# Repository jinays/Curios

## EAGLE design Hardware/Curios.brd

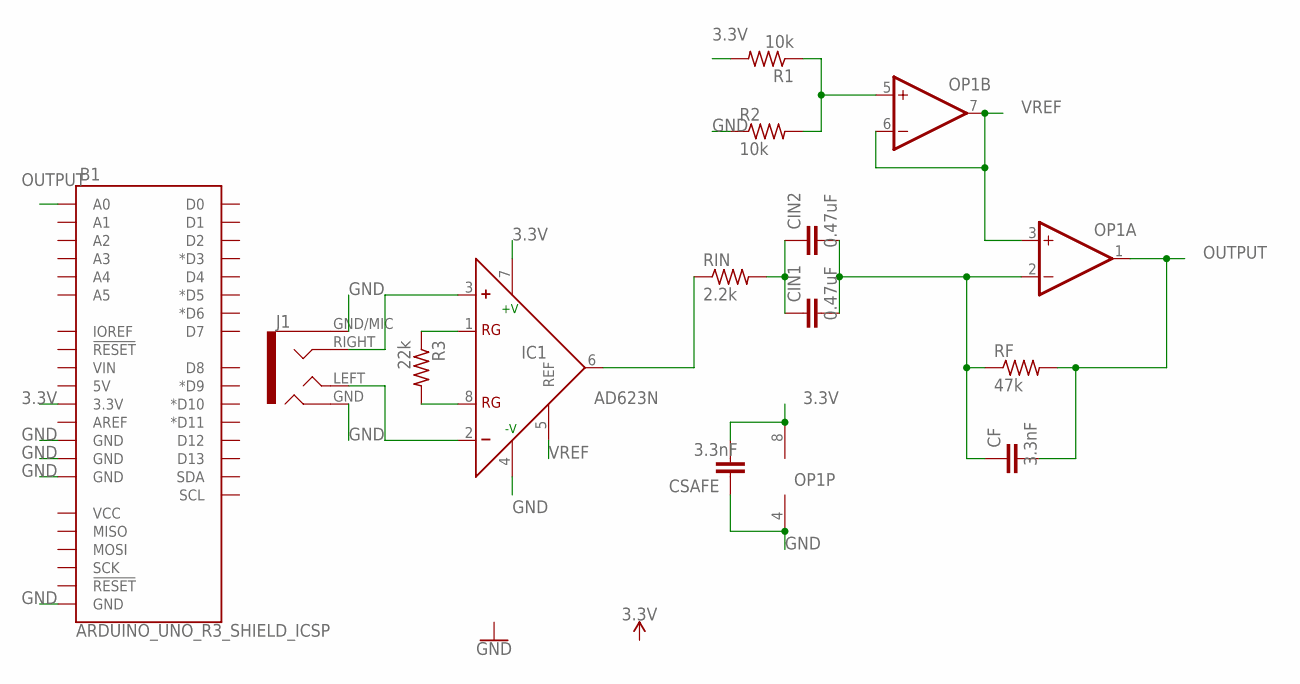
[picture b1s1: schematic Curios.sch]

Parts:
B1: ARDUINO_UNO_R3_SHIELD_ICSP; UNO_R3_SHIELD_ICSP
CF: 3.3nF; C0603
CIN1, CIN2: 0.47uF; C0603
CSAFE: 3.3nF; C0603
IC1: AD623N; DIL08
J1: AUDIO_JACK_TRRSSMD_RA; AUDIO_JACK_3.5MM_TRRS_SMD_RA
OP1: OP-DUALR; SO8
R1, R2: 10k; R0603
R3: 22k; R0603
RF: 47k; R0603
RIN: 2.2k; R0603

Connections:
3.3V: B1.3.3V, CSAFE.2, IC1.7 (+V), OP1.8 (V+), R1.2
GND: B1.GND@0 (GND), B1.GND@1 (GND), B1.GND@2 (GND), B1.GND_ICSP (GND), CSAFE.1, IC1.4 (-V), J1.GND (RING2), J1.GND/MIC (SLEEVE), OP1.4 (V-), R2.1
unnamed: CIN1.1, CIN2.1, RIN.2
unnamed: IC1.3 (+), J1.RIGHT (RING1)
unnamed: OP1.5 (+IN), R1.1, R2.2
unnamed: IC1.6 (OUT), RIN.1
unnamed: IC1.1 (RG), R3.1
unnamed: CF.1, CIN1.2, CIN2.2, OP1.2 (-IN), RF.1
unnamed: IC1.8 (RG), R3.2
unnamed: IC1.2 (-), J1.LEFT (TIP)
OUTPUT: B1.A0, CF.2, OP1.1 (OUT), RF.2
VREF: IC1.5 (REF), OP1.3 (+IN), OP1.6 (-IN), OP1.7 (OUT)

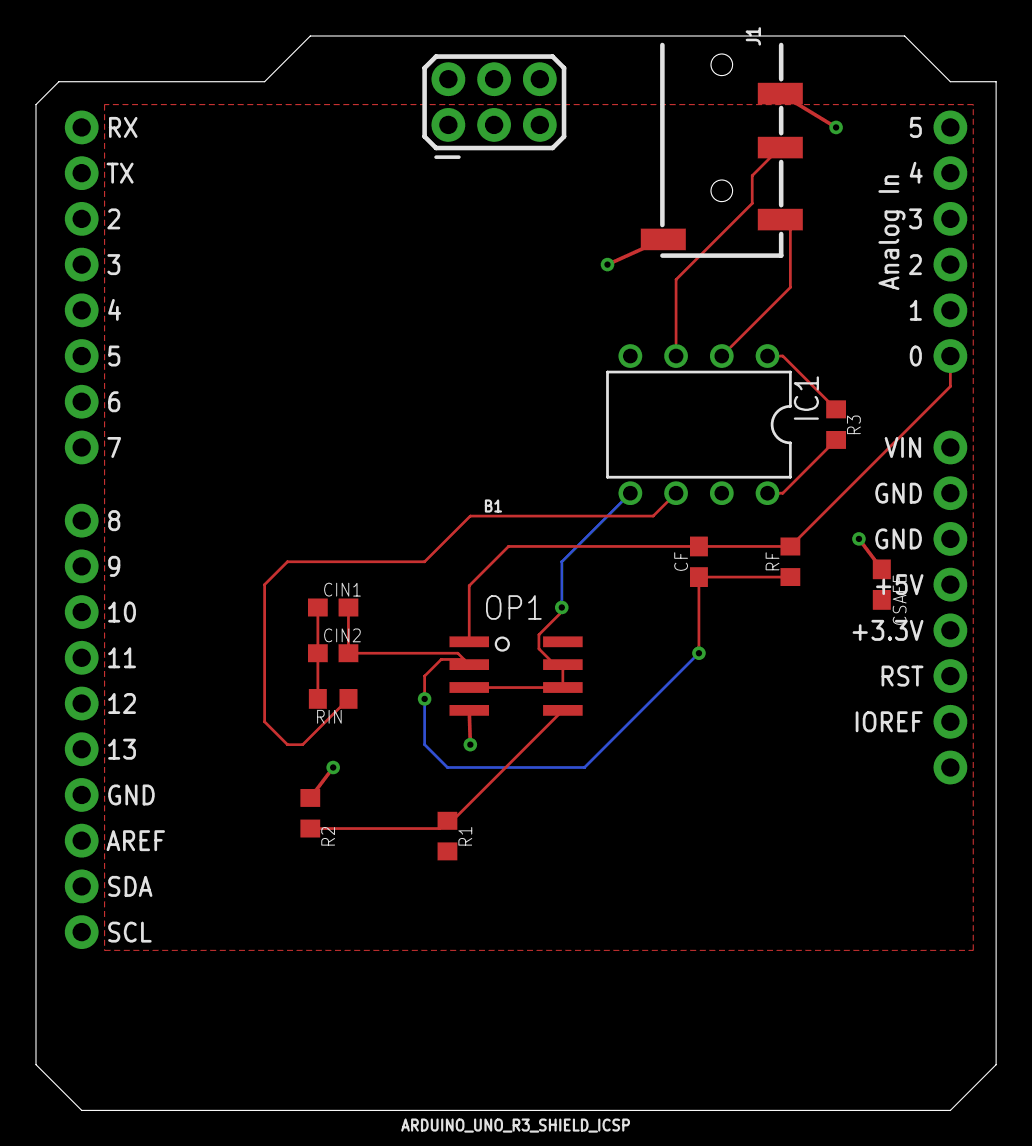
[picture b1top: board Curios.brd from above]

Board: 2 copper layers, 53.3 x 59.7 mm, 13 parts (0 on the bottom side), 12 nets.

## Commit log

2022-09-08 intro
2022-09-14 Arduino sketch
2022-09-14 Eagle schematics
2022-09-14 Eagle board
2022-09-15 update week 2
2022-09-28 Week6 update
2022-09-29 Week 6 update
2022-10-05 Week7
2022-10-19 added CAM outputs
